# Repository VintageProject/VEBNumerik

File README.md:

# VEBNumerik
Additional modules and documentation for the VEB Numerik line of electronics kits, like the Elektronik System 100 or 150.

These kits were produced by VEB Numerik in Karl-Marx-Stadt, former GDR.

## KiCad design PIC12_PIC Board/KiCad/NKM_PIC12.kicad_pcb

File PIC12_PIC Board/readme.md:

Nothing fancy. Just a way to use a PIC12 (e.g. PIC12F675) with your NKM Numerik kit.
You're more of an ATTiny person? Take a look at the ATTiny85 board, then. :)

This board is a breakout for the PIC12 and it sports a handy ICSP header as per the PICKit standard. I left the "N.C." in as I found that the programming cables often come in a six wire configuration and I wanted to accommodate those without modification.

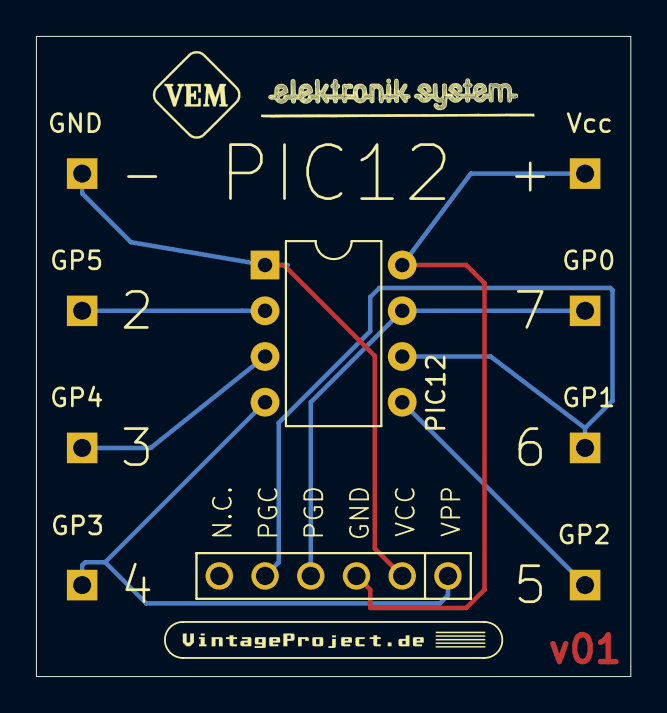
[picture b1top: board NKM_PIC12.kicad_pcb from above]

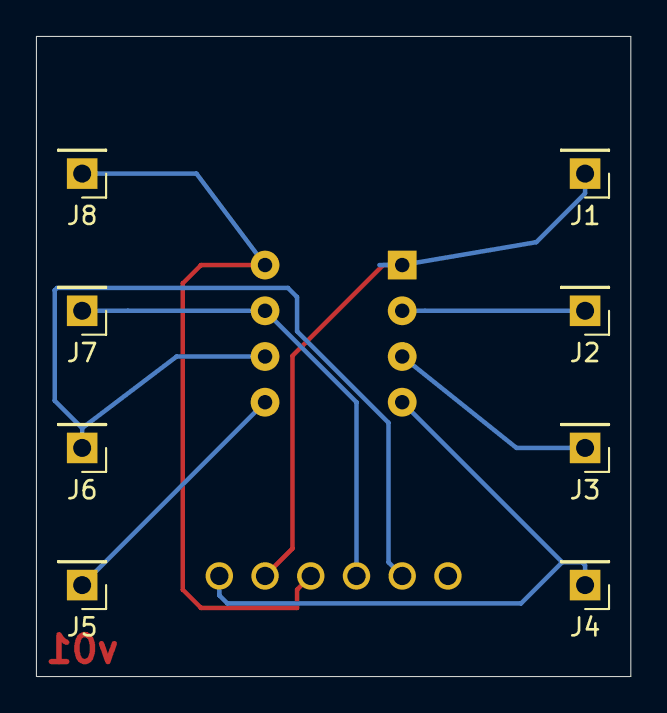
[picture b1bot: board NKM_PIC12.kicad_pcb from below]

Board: 2 copper layers, 33.0 x 35.6 mm, 10 parts (8 on the bottom side), 8 nets.

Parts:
1: ICSP_MICROCHIP
J1, J2, J3, J4, J5, J6, J7, J8: Conn_01x01_Male; PinHeader_1x01_P2.54mm_Vertical
U1: PIC12; DIP-8_W7.62mm

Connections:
/GP2: J5.1, U1.5
/GP4: J3.1, U1.3
/GP5: J2.1, U1.2
/PGC: 1.5, J6.1, U1.6
/PGD: 1.4, J7.1, U1.7
/VPP: 1.1, J4.1, U1.4
GND: 1.3, J8.1, U1.8
VCC: 1.2, J1.1, U1.1

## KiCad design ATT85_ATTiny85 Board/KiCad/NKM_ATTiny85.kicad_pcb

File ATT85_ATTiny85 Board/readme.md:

Nothing fancy. Just a way to use an ATTiny85 with your NKM Numerik kit.
You're more of a PIC person? Take a look at the PIC board, then. :)

This board is a breakout for the ATTiny and it sports a handy ISP header as per the 6-pin standard. If you want to use the 10-pin header, you'll have to use an adapter or change the board design.

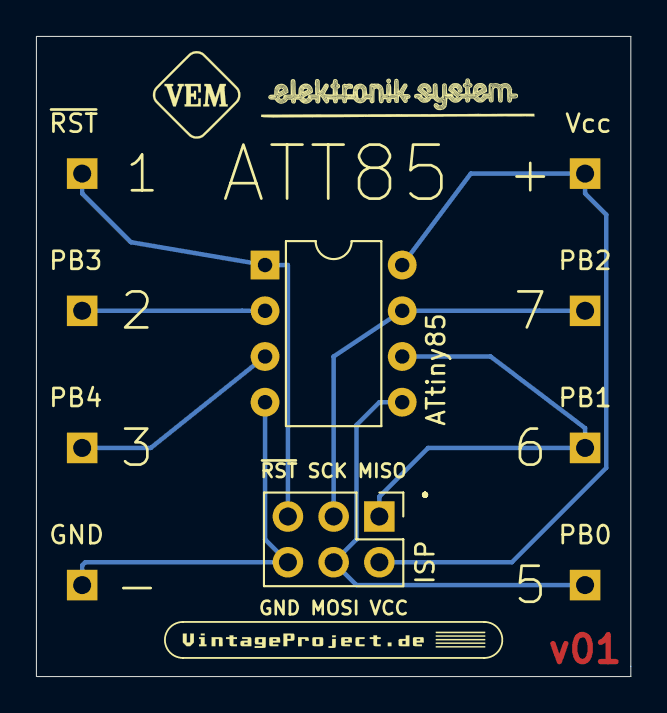
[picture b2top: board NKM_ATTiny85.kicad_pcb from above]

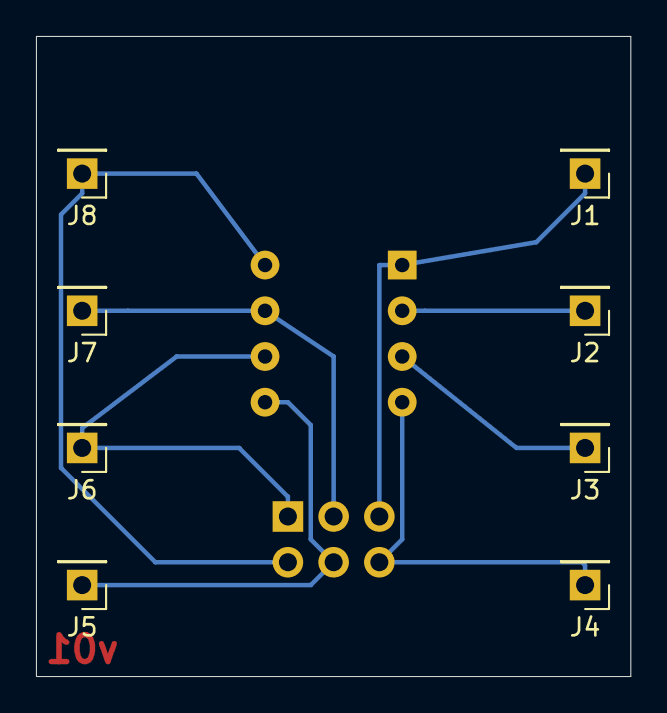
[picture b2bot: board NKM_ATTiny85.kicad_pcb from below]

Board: 2 copper layers, 33.0 x 35.6 mm, 10 parts (8 on the bottom side), 8 nets.

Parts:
ISP: AVR-ISP-6; PinHeader_2x03_P2.54mm_Vertical
J1, J2, J3, J4, J5, J6, J7, J8: Conn_01x01_Male; PinHeader_1x01_P2.54mm_Vertical
U1: ATtiny85; DIP-8_W7.62mm

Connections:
/MISO: ISP.1, J6.1, U1.6
/MOSI: ISP.4, J5.1, U1.5
/SCK: ISP.3, J7.1, U1.7
/~RST: ISP.5, J1.1, U1.1
GND: ISP.6, J4.1, U1.4
unnamed: J2.1, U1.2
unnamed: J3.1, U1.3
VCC: ISP.2, J8.1, U1.8

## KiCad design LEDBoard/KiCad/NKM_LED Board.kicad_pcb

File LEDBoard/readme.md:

An additional indicator board to use with the NKM Numerik's breadboard section.
It'll plug in a full row on any of the two breadboards and can be used for outputs up to the 9V of the double battery pack.
The LEDs, if equipped with 330R..390R (for 5V) will see around 20mA then. You might want to use larger resistors just in case.

As for the header pins, they're spaced 7.5 mm apart, but for short stretches you can get away with regular 2.54mm header pins. If you use angled header pins, remove every second and third pin from the plastic holder. Also put angled headers on the back of the PCB, unlike the 3D render shows. This will allow for better seating and a slightly angled positioning of the board.

The connectors ("GND") on the side allow for use of jumper cables, so that you can connect the common cathode of the LEDs around the breadboards and as per the circuit you're building. One pad is slightly separated intentionally, as my approach is to have one fixed jumper for the LEDs and additional pins for dupont jumpers, that connect to the other LED board or offer additional GNDs for the circuit.

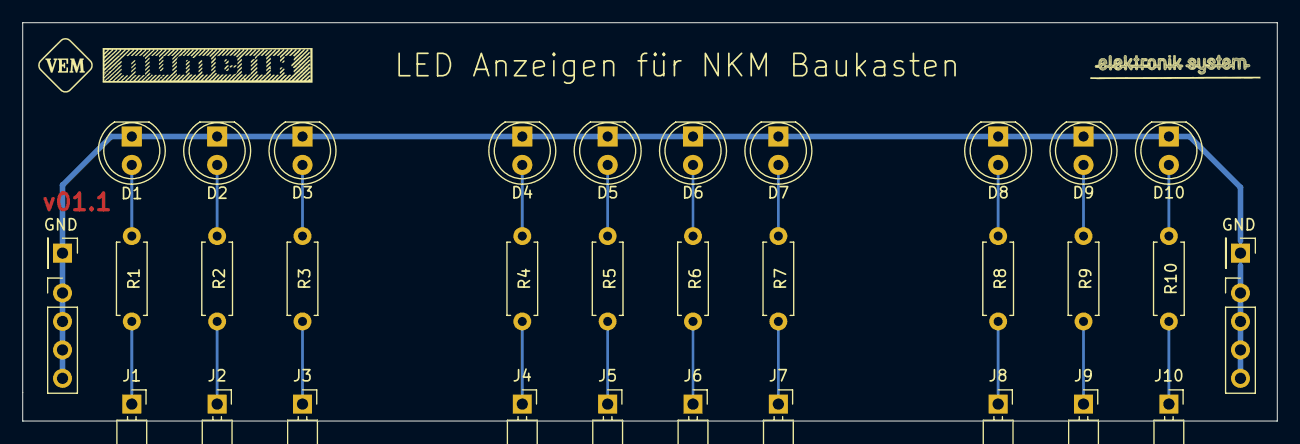
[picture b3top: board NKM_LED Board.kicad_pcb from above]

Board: 2 copper layers, 112.0 x 35.6 mm, 32 parts (0 on the bottom side), 21 nets.

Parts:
D1, D2, D3, D4, D5, D6, D7, D8, D9, D10: RED; LED_D5.0mm
GND: Conn_01x01_Male; PinHeader_1x01_P2.54mm_Vertical
GND#2: Conn_01x01_Male; PinHeader_1x01_P2.54mm_Vertical
J1, J2, J3, J4, J5, J6, J7, J8, J9, J10: Conn_01x01_Male; PinHeader_1x01_P2.54mm_Horizontal
R1, R2, R3, R4, R5, R6, R7, R8, R9, R10: 330; R_Axial_DIN0207_L6.3mm_D2.5mm_P7.62mm_Horizontal

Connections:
GND: D1.1, D2.1, D3.1, D4.1, D5.1, D6.1, D7.1, D8.1, D9.1, D10.1, GND.1, GND#2.1
unnamed: D1.2, R1.1
unnamed: D2.2, R2.1
unnamed: D3.2, R3.1
unnamed: D4.2, R4.1
unnamed: D5.2, R5.1
unnamed: D6.2, R6.1
unnamed: D7.2, R7.1
unnamed: D8.2, R8.1
unnamed: D9.2, R9.1
unnamed: D10.2, R10.1
unnamed: J1.1, R1.2
unnamed: J2.1, R2.2
unnamed: J3.1, R3.2
unnamed: J4.1, R4.2
unnamed: J5.1, R5.2
unnamed: J6.1, R6.2
unnamed: J7.1, R7.2
unnamed: J8.1, R8.2
unnamed: J9.1, R9.2
unnamed: J10.1, R10.2

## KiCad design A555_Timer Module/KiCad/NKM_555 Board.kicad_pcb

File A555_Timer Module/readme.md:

This is what every electronics kit nowadays has to have:
A module with the famous 555 timer IC.
What else can I say about this? :)

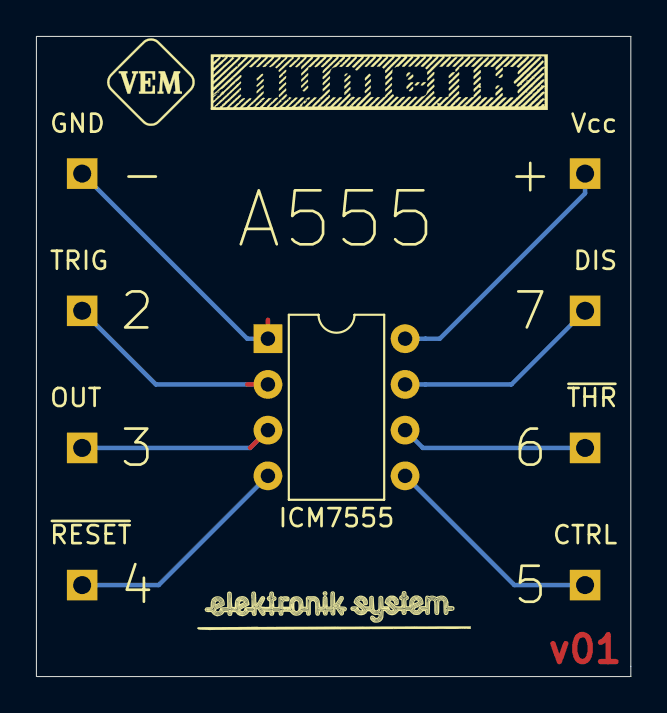
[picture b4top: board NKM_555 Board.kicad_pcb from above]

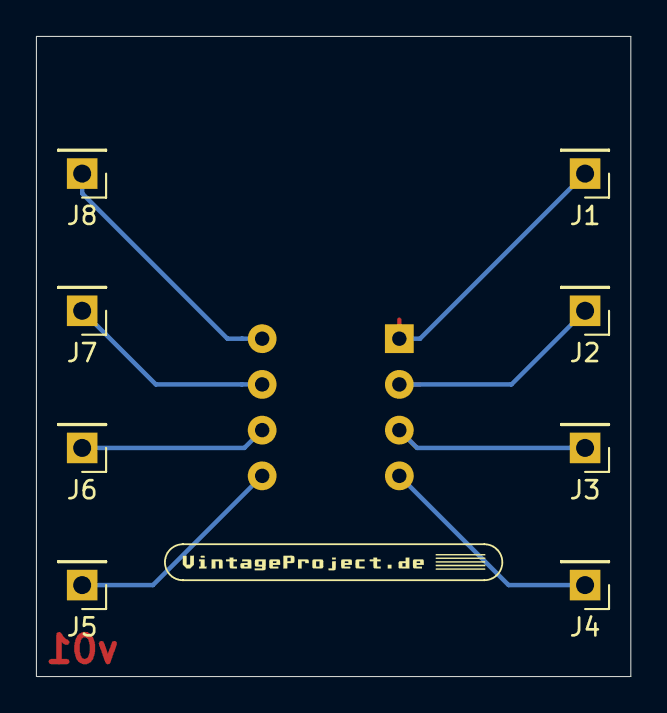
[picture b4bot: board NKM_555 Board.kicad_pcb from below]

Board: 2 copper layers, 33.0 x 35.6 mm, 9 parts (8 on the bottom side), 8 nets.

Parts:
J1, J2, J3, J4, J5, J6, J7, J8: Conn_01x01_Male; PinHeader_1x01_P2.54mm_Vertical
U1: ICM7555; DIP-8_W7.62mm

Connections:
unnamed: J1.1, U1.1
unnamed: J2.1, U1.2
unnamed: J3.1, U1.3
unnamed: J4.1, U1.4
unnamed: J5.1, U1.5
unnamed: J6.1, U1.6
unnamed: J7.1, U1.7
unnamed: J8.1, U1.8

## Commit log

2019-05-31 Create A5_Readme
2019-05-31 Update A5_Readme
2019-05-31 Rename A5_Readme to readme.md
